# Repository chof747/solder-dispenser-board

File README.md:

## solder-dispenser-board

This is the connection board for a solder paste dispenser featuring a DC motor and breaking out to the electronics
which are on a separate board and connect to the dispenser via an RJ11 connector

## Revision History:

- **v1.0**: Initial version (filed for fabrication: 13.03.2024)

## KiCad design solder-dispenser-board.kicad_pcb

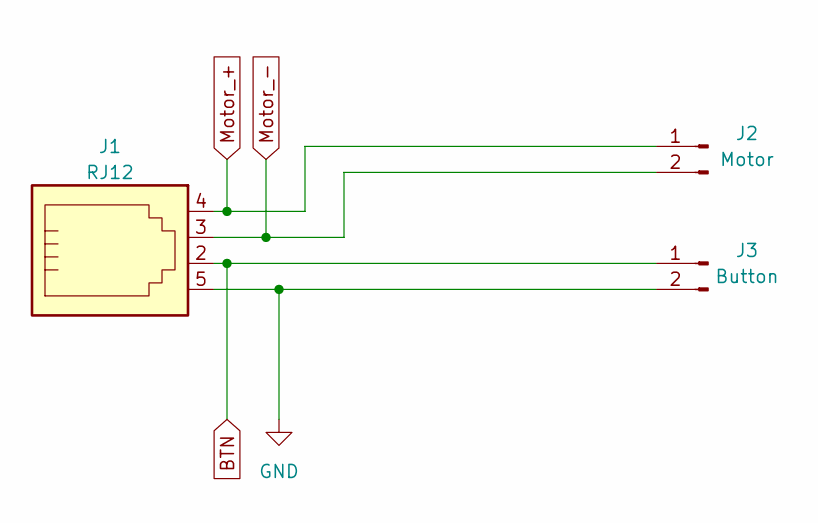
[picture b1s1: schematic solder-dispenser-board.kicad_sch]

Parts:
J1: RJ12; RJ12_Amphenol_54601
J2: Motor; PinHeader_1x02_P2.54mm_Horizontal
J3: Button; PinHeader_1x02_P2.54mm_Horizontal

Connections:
BTN: J1.2, J3.1
GND: J1.5, J3.2
Motor_+: J1.4, J2.1
Motor_-: J1.3, J2.2

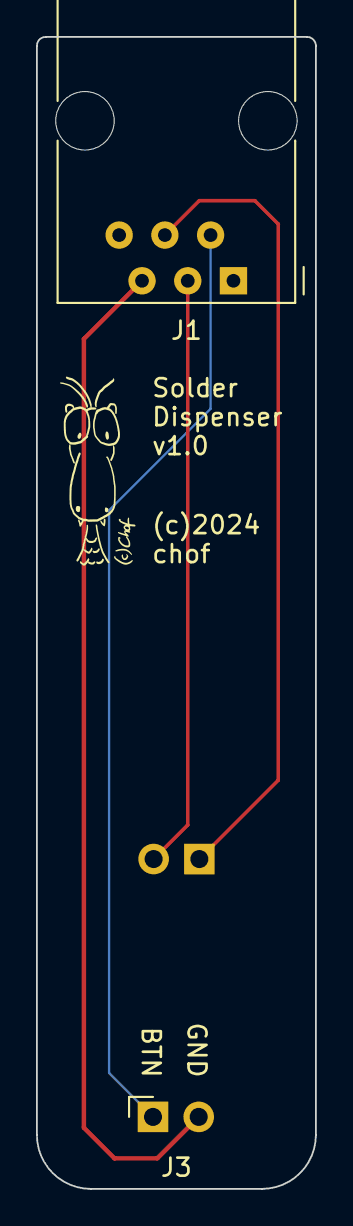
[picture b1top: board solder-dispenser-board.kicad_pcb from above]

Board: 2 copper layers, 15.5 x 64.0 mm, 3 parts (1 on the bottom side), 4 nets.

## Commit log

2024-03-14 Version 1.0 sent to fab-house + update to KiCad 8

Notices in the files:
solder-dispenser-board.kicad_pcb:
(c)2024
